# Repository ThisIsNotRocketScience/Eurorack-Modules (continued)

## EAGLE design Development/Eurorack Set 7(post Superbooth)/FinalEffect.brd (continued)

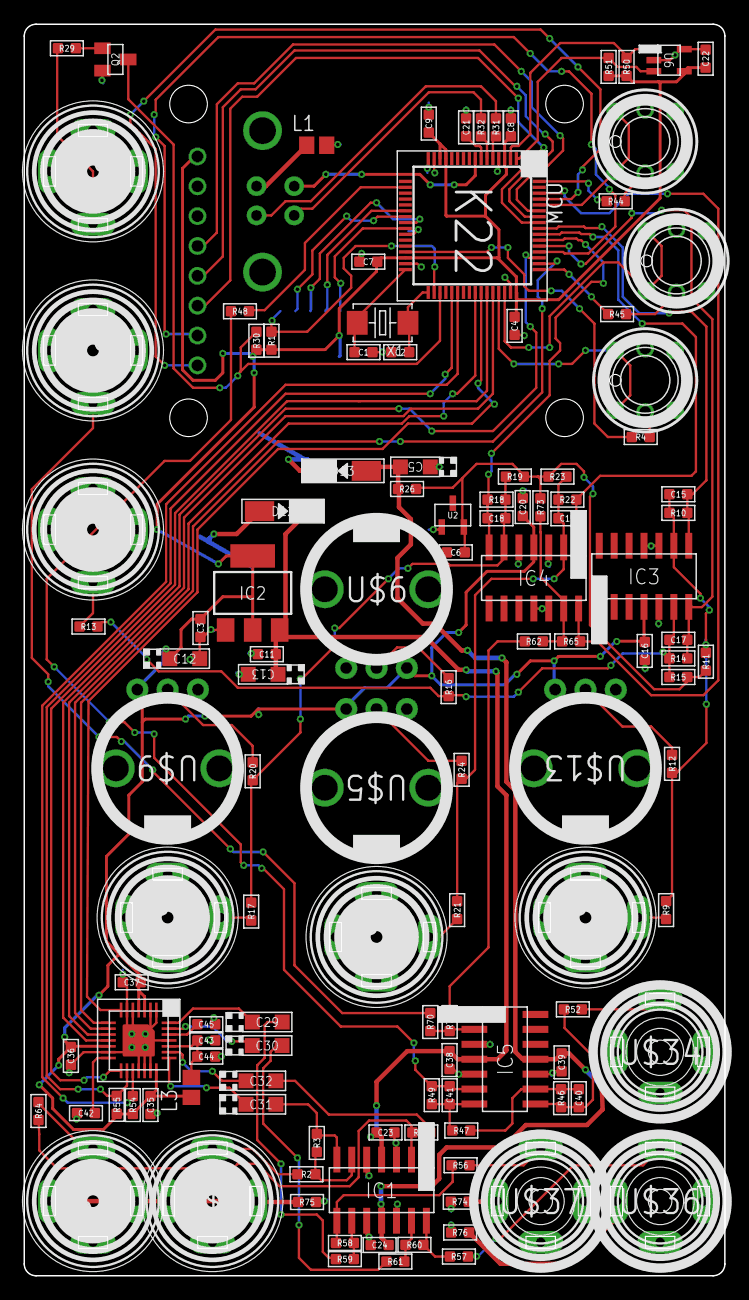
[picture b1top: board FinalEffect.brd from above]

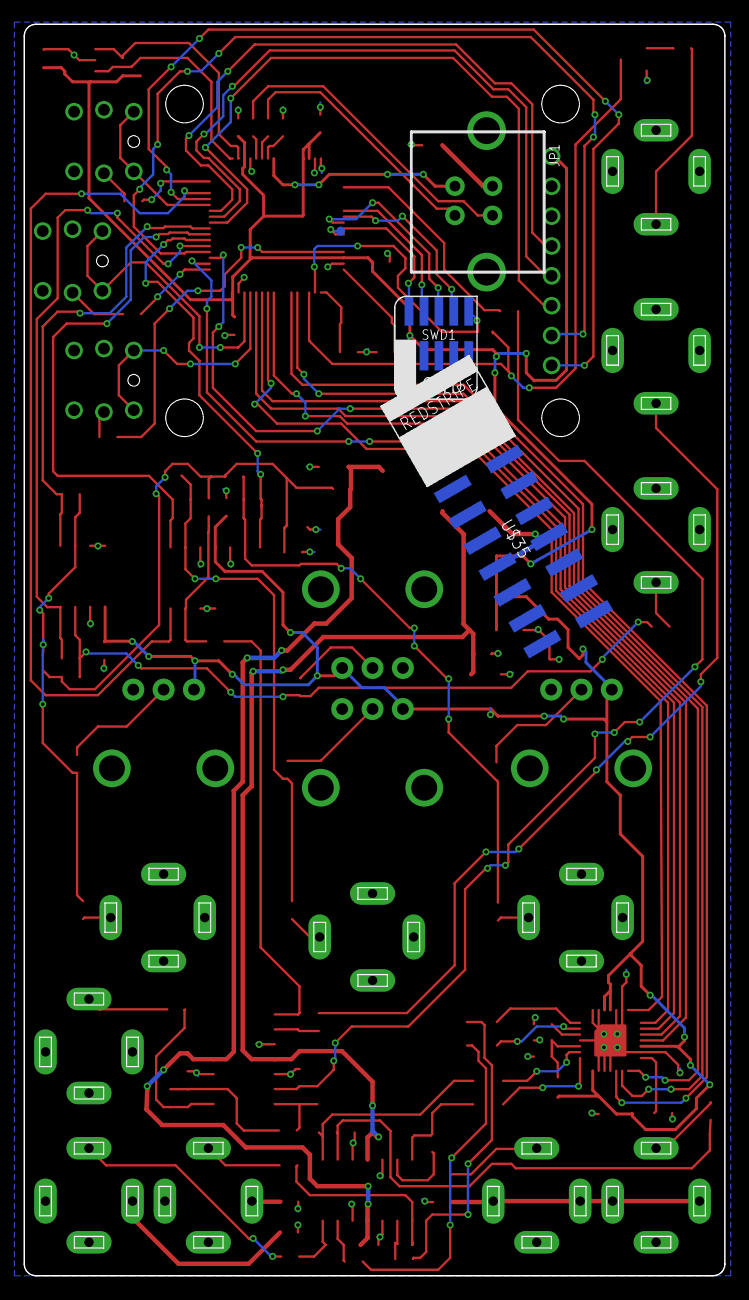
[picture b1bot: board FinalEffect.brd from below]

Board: 2 copper layers, 59.6 x 106.5 mm, 128 parts (4 on the bottom side), 100 nets.

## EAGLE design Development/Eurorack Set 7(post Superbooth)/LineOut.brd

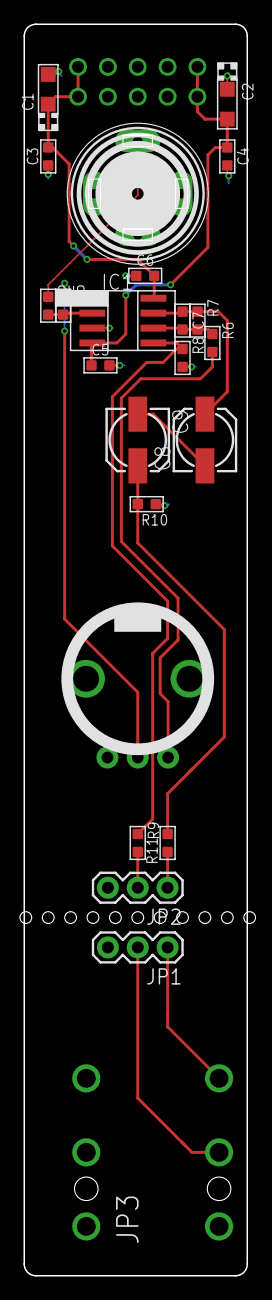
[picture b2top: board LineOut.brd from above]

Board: 2 copper layers, 19.0 x 106.5 mm, 25 parts (1 on the bottom side), 17 nets.

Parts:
C1, C2: 10uF; AVX-A
C3, C4, C5, C6: 100nF; C0603
C7: 22p; C0603
C8, C9: 220uF; 153CLV-0505
IC1: NE5532D; SO08
JP1, JP2: 1X03
JP3: AUDIO-JACK-.25-INCH-HORIZ-PTH
R2: 100k; R0603
R5: 220k; R0603
R6, R7: 4.7k; R0603
R8, R9: 27; R0603
R10: 22k; R0603
R11: 56; R0603
U$1: POWER_SIMPLE10; POWER_10
U$3: 10k; OG-POTS_ALPS_POT_VERTICAL
U$5: PJ-341; 3.5MM-JACK-SWITCH-13MM-INPUT
U$6: EURORACK_PCB4HP; EURORACK4HPPCB

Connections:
+12V: C1.+, C3.2, C6.2, IC1.8, U$1.9, U$1.10
-12V: C2.-, C4.1, C5.1, IC1.4, U$1.1, U$1.2
GND: C1.-, C2.+, C3.1, C4.2, C5.2, C6.1, IC1.3, JP2.3, R8.2, R10.1, U$1.3, U$1.4, U$1.5, U$1.6, U$1.7, U$1.8, U$3.P$1, U$5.RING@3, U$5.SWITCH@3
GND2: JP1.3, JP3.P$2, JP3.P$5
unnamed: JP2.1, R11.1
unnamed: JP1.1, JP3.P$6
unnamed: C9.+, R10.2, R11.2
unnamed: C7.1, C8.+, IC1.7, R7.1
unnamed: IC1.5, R8.1, R9.1
unnamed: JP2.2, R9.2
unnamed: C7.2, IC1.6, R6.1, R7.2
unnamed: IC1.2, R2.2, R5.2
unnamed: IC1.1, R5.1, U$3.P$2
unnamed: R6.2, U$3.P$3
unnamed: C8.-, C9.-
unnamed: R2.1, U$5.TIP@3
unnamed: JP1.2, JP3.P$4

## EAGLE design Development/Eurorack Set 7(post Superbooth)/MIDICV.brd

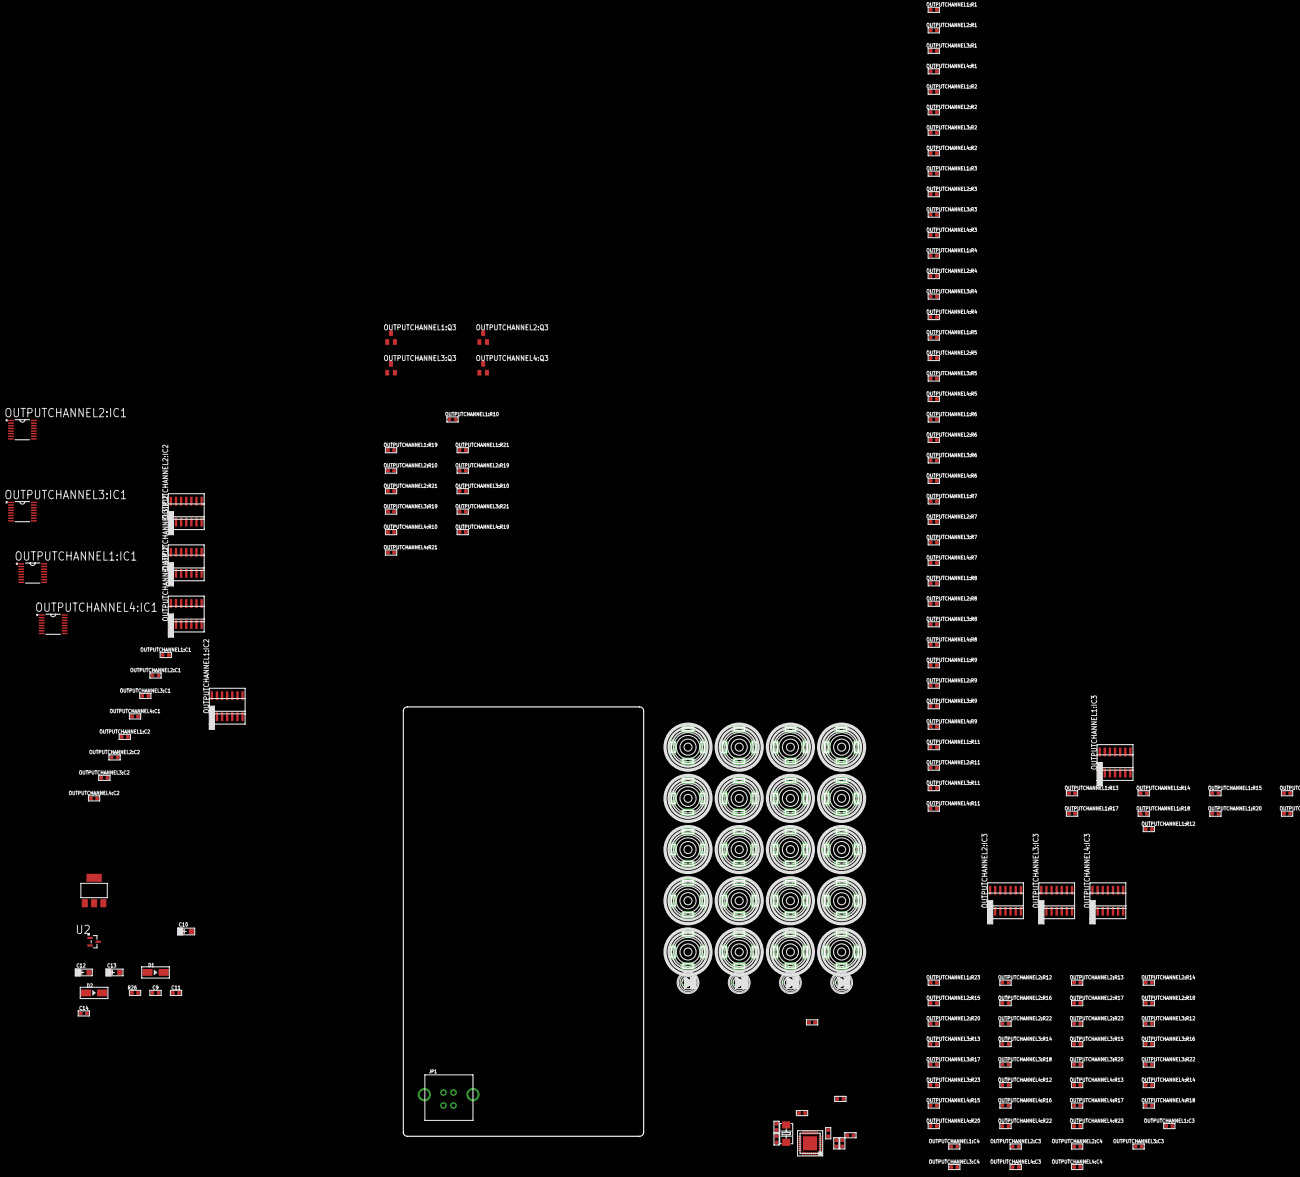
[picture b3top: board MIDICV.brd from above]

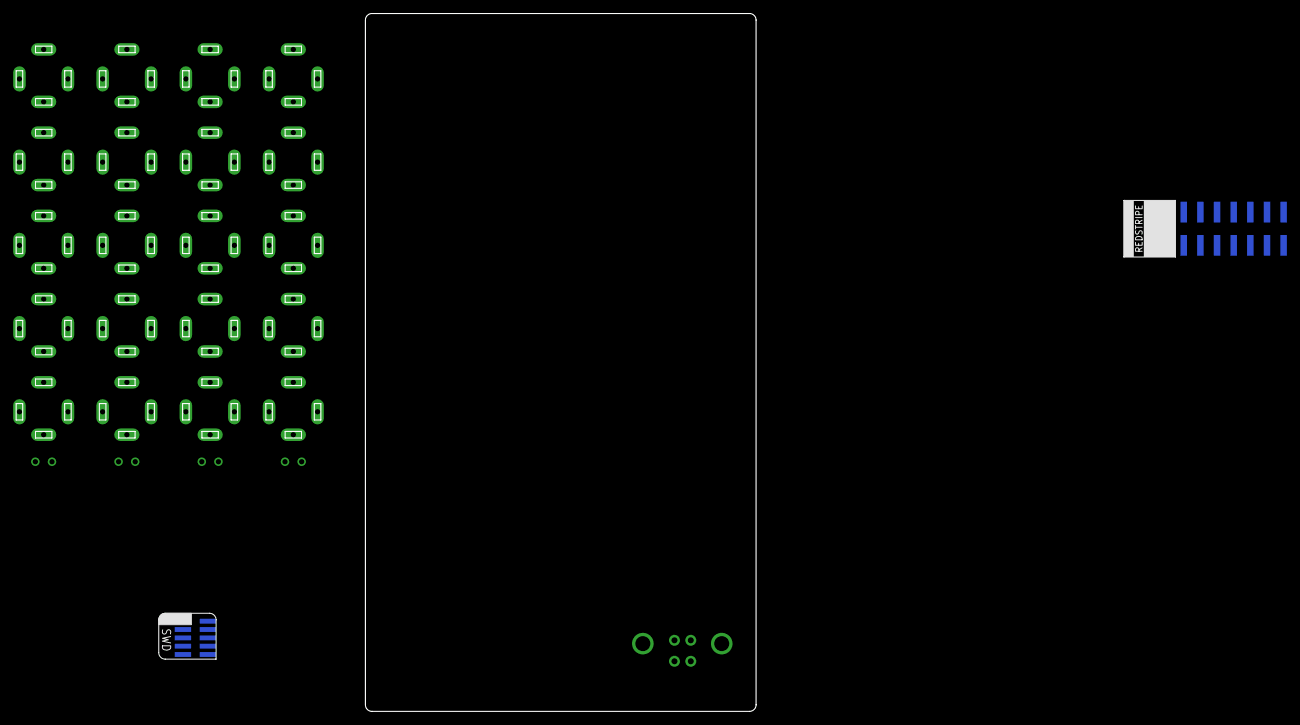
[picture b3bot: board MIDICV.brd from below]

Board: 2 copper layers, 174 parts (2 on the bottom side), 128 nets, no tracks yet.

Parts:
C1, C2, C3, C4, C6, C7, C8: C0603
C9, C11, C14: 100nF; C0603
C10, C12, C13: 10uF; AVX-A
D1, D2: MRA4004T3G; DO-214AC
IC1: LD1117AS33TR; SOT223
J14: POWERSMT; 2X08_SMT_HEADER
JP1: USBPTH-VERTICAL; USB-B-PTH-VERTICAL
OUTPUTCHANNEL1:C1, OUTPUTCHANNEL1:C2, OUTPUTCHANNEL1:C3, OUTPUTCHANNEL1:C4, OUTPUTCHANNEL2:C1, OUTPUTCHANNEL2:C2, OUTPUTCHANNEL2:C3, OUTPUTCHANNEL2:C4, OUTPUTCHANNEL3:C1, OUTPUTCHANNEL3:C2, OUTPUTCHANNEL3:C3, OUTPUTCHANNEL3:C4, OUTPUTCHANNEL4:C1, OUTPUTCHANNEL4:C2, OUTPUTCHANNEL4:C3, OUTPUTCHANNEL4:C4: C0603
OUTPUTCHANNEL1:D40, OUTPUTCHANNEL2:D40, OUTPUTCHANNEL3:D40, OUTPUTCHANNEL4:D40: yellow; 3MMLED
OUTPUTCHANNEL1:IC1, OUTPUTCHANNEL2:IC1, OUTPUTCHANNEL3:IC1, OUTPUTCHANNEL4:IC1: DAC8564; SOP65P640X110-16N
OUTPUTCHANNEL1:IC2, OUTPUTCHANNEL1:IC3, OUTPUTCHANNEL2:IC2, OUTPUTCHANNEL2:IC3, OUTPUTCHANNEL3:IC2, OUTPUTCHANNEL3:IC3, OUTPUTCHANNEL4:IC2, OUTPUTCHANNEL4:IC3: TL074D; SO14
OUTPUTCHANNEL1:Q3, OUTPUTCHANNEL2:Q3, OUTPUTCHANNEL3:Q3, OUTPUTCHANNEL4:Q3: MMBT3904; SOT23-BEC
OUTPUTCHANNEL1:R1, OUTPUTCHANNEL1:R2, OUTPUTCHANNEL1:R3, OUTPUTCHANNEL1:R4, OUTPUTCHANNEL1:R5, OUTPUTCHANNEL1:R6, OUTPUTCHANNEL1:R7, OUTPUTCHANNEL1:R8, OUTPUTCHANNEL1:R9, OUTPUTCHANNEL1:R11, OUTPUTCHANNEL1:R12, OUTPUTCHANNEL1:R13, OUTPUTCHANNEL1:R14, OUTPUTCHANNEL1:R15, OUTPUTCHANNEL1:R16, OUTPUTCHANNEL1:R17, OUTPUTCHANNEL1:R18, OUTPUTCHANNEL1:R20, OUTPUTCHANNEL1:R21, OUTPUTCHANNEL1:R22, OUTPUTCHANNEL1:R23, OUTPUTCHANNEL2:R1, OUTPUTCHANNEL2:R2, OUTPUTCHANNEL2:R3, OUTPUTCHANNEL2:R4, OUTPUTCHANNEL2:R5, OUTPUTCHANNEL2:R6, OUTPUTCHANNEL2:R7, OUTPUTCHANNEL2:R8, OUTPUTCHANNEL2:R9, OUTPUTCHANNEL2:R11, OUTPUTCHANNEL2:R12, OUTPUTCHANNEL2:R13, OUTPUTCHANNEL2:R14, OUTPUTCHANNEL2:R15, OUTPUTCHANNEL2:R16, OUTPUTCHANNEL2:R17, OUTPUTCHANNEL2:R18, OUTPUTCHANNEL2:R20, OUTPUTCHANNEL2:R21, OUTPUTCHANNEL2:R22, OUTPUTCHANNEL2:R23, OUTPUTCHANNEL3:R1, OUTPUTCHANNEL3:R2, OUTPUTCHANNEL3:R3, OUTPUTCHANNEL3:R4, OUTPUTCHANNEL3:R5, OUTPUTCHANNEL3:R6, OUTPUTCHANNEL3:R7, OUTPUTCHANNEL3:R8, OUTPUTCHANNEL3:R9, OUTPUTCHANNEL3:R11, OUTPUTCHANNEL3:R12, OUTPUTCHANNEL3:R13, OUTPUTCHANNEL3:R14, OUTPUTCHANNEL3:R15, OUTPUTCHANNEL3:R16, OUTPUTCHANNEL3:R17, OUTPUTCHANNEL3:R18, OUTPUTCHANNEL3:R20, OUTPUTCHANNEL3:R21, OUTPUTCHANNEL3:R22, OUTPUTCHANNEL3:R23, OUTPUTCHANNEL4:R1, OUTPUTCHANNEL4:R2, OUTPUTCHANNEL4:R3, OUTPUTCHANNEL4:R4, OUTPUTCHANNEL4:R5, OUTPUTCHANNEL4:R6, OUTPUTCHANNEL4:R7, OUTPUTCHANNEL4:R8, OUTPUTCHANNEL4:R9, OUTPUTCHANNEL4:R11, OUTPUTCHANNEL4:R12, OUTPUTCHANNEL4:R13, OUTPUTCHANNEL4:R14, OUTPUTCHANNEL4:R15, OUTPUTCHANNEL4:R16, OUTPUTCHANNEL4:R17, OUTPUTCHANNEL4:R18, OUTPUTCHANNEL4:R20, OUTPUTCHANNEL4:R21, OUTPUTCHANNEL4:R22, OUTPUTCHANNEL4:R23: 100k; R0603
OUTPUTCHANNEL1:R10, OUTPUTCHANNEL2:R10, OUTPUTCHANNEL3:R10, OUTPUTCHANNEL4:R10: 56; R0603
OUTPUTCHANNEL1:R19, OUTPUTCHANNEL2:R19, OUTPUTCHANNEL3:R19, OUTPUTCHANNEL4:R19: 10k; R0603
OUTPUTCHANNEL1:U$1, OUTPUTCHANNEL1:U$2, OUTPUTCHANNEL1:U$3, OUTPUTCHANNEL1:U$4, OUTPUTCHANNEL1:U$5, OUTPUTCHANNEL2:U$1, OUTPUTCHANNEL2:U$2, OUTPUTCHANNEL2:U$3, OUTPUTCHANNEL2:U$4, OUTPUTCHANNEL2:U$5, OUTPUTCHANNEL3:U$1, OUTPUTCHANNEL3:U$2, OUTPUTCHANNEL3:U$3, OUTPUTCHANNEL3:U$4, OUTPUTCHANNEL3:U$5, OUTPUTCHANNEL4:U$1, OUTPUTCHANNEL4:U$2, OUTPUTCHANNEL4:U$3, OUTPUTCHANNEL4:U$4, OUTPUTCHANNEL4:U$5: PJ-341; 3.5MM-JACK-SWITCH-13MM-OUTPUT
R1, R2: 33; R0603
R26: 10k; R0603
SWD1: CORTEX_SWD; M50-3600542
U2: LM4040DIM3-5.0; SOT95P237X112-3N
U$1: KL26X32VFM4; QFN-32
U$2: EURORACK_PCB12HP; EURORACK12HPPCB
X2: CRYSTAL-0500290P1; 2P-SMD-5.0X3.2

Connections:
3.3V: C1.1, C2.1, C3.1, C4.1, C8.1, C9.2, C12.+, IC1.2, IC1.4, SWD1.1, U$1.7, U$1.15
12V: C11.2, C13.+, D1.2, IC1.3, OUTPUTCHANNEL1:C1.1, OUTPUTCHANNEL1:C3.1, OUTPUTCHANNEL1:IC2.4, OUTPUTCHANNEL1:IC3.4, OUTPUTCHANNEL1:R19.2, OUTPUTCHANNEL2:C1.1, OUTPUTCHANNEL2:C3.1, OUTPUTCHANNEL2:IC2.4, OUTPUTCHANNEL2:IC3.4, OUTPUTCHANNEL2:R19.2, OUTPUTCHANNEL3:C1.1, OUTPUTCHANNEL3:C3.1, OUTPUTCHANNEL3:IC2.4, OUTPUTCHANNEL3:IC3.4, OUTPUTCHANNEL3:R19.2, OUTPUTCHANNEL4:C1.1, OUTPUTCHANNEL4:C3.1, OUTPUTCHANNEL4:IC2.4, OUTPUTCHANNEL4:IC3.4, OUTPUTCHANNEL4:R19.2
-12V: C10.-, D2.1, OUTPUTCHANNEL1:C2.1, OUTPUTCHANNEL1:C4.1, OUTPUTCHANNEL1:IC2.11, OUTPUTCHANNEL1:IC3.11, OUTPUTCHANNEL2:C2.1, OUTPUTCHANNEL2:C4.1, OUTPUTCHANNEL2:IC2.11, OUTPUTCHANNEL2:IC3.11, OUTPUTCHANNEL3:C2.1, OUTPUTCHANNEL3:C4.1, OUTPUTCHANNEL3:IC2.11, OUTPUTCHANNEL3:IC3.11, OUTPUTCHANNEL4:C2.1, OUTPUTCHANNEL4:C4.1, OUTPUTCHANNEL4:IC2.11, OUTPUTCHANNEL4:IC3.11, R26.1
BUTTON4: SWD1.10, U$1.19
EXTCV: J14.13, J14.14, OUTPUTCHANNEL1:R2.2, OUTPUTCHANNEL1:U$1.TIP@3
EXTGATE: J14.15, J14.16, OUTPUTCHANNEL1:R10.2, OUTPUTCHANNEL1:R21.1
GND: C1.2, C2.2, C3.2, C4.2, C6.1, C7.2, C8.2, C9.1, C10.+, C11.1, C12.-, C13.-, C14.1, IC1.1, J14.3, J14.4, J14.5, J14.6, J14.7, J14.8, JP1.GND, OUTPUTCHANNEL1:C1.2, OUTPUTCHANNEL1:C2.2, OUTPUTCHANNEL1:C3.2, OUTPUTCHANNEL1:C4.2, OUTPUTCHANNEL1:IC1.6, OUTPUTCHANNEL1:IC2.3, OUTPUTCHANNEL1:IC2.5, OUTPUTCHANNEL1:IC2.10, OUTPUTCHANNEL1:IC2.12, OUTPUTCHANNEL1:IC3.3, OUTPUTCHANNEL1:IC3.5, OUTPUTCHANNEL1:IC3.10, OUTPUTCHANNEL1:IC3.12, OUTPUTCHANNEL1:Q3.E, OUTPUTCHANNEL1:U$1.RING@3, OUTPUTCHANNEL1:U$2.RING@3, OUTPUTCHANNEL1:U$3.RING@3, OUTPUTCHANNEL1:U$4.RING@3, OUTPUTCHANNEL1:U$5.RING@3, OUTPUTCHANNEL2:C1.2, OUTPUTCHANNEL2:C2.2, OUTPUTCHANNEL2:C3.2, OUTPUTCHANNEL2:C4.2, OUTPUTCHANNEL2:IC1.6, OUTPUTCHANNEL2:IC2.3, OUTPUTCHANNEL2:IC2.5, OUTPUTCHANNEL2:IC2.10, OUTPUTCHANNEL2:IC2.12, OUTPUTCHANNEL2:IC3.3, OUTPUTCHANNEL2:IC3.5, OUTPUTCHANNEL2:IC3.10, OUTPUTCHANNEL2:IC3.12, OUTPUTCHANNEL2:Q3.E, OUTPUTCHANNEL2:U$1.RING@3, OUTPUTCHANNEL2:U$2.RING@3, OUTPUTCHANNEL2:U$3.RING@3, OUTPUTCHANNEL2:U$4.RING@3, OUTPUTCHANNEL2:U$5.RING@3, OUTPUTCHANNEL3:C1.2, OUTPUTCHANNEL3:C2.2, OUTPUTCHANNEL3:C3.2, OUTPUTCHANNEL3:C4.2, OUTPUTCHANNEL3:IC1.6, OUTPUTCHANNEL3:IC2.3, OUTPUTCHANNEL3:IC2.5, OUTPUTCHANNEL3:IC2.10, OUTPUTCHANNEL3:IC2.12, OUTPUTCHANNEL3:IC3.3, OUTPUTCHANNEL3:IC3.5, OUTPUTCHANNEL3:IC3.10, OUTPUTCHANNEL3:IC3.12, OUTPUTCHANNEL3:Q3.E, OUTPUTCHANNEL3:U$1.RING@3, OUTPUTCHANNEL3:U$2.RING@3, OUTPUTCHANNEL3:U$3.RING@3, OUTPUTCHANNEL3:U$4.RING@3, OUTPUTCHANNEL3:U$5.RING@3, OUTPUTCHANNEL4:C1.2, OUTPUTCHANNEL4:C2.2, OUTPUTCHANNEL4:C3.2, OUTPUTCHANNEL4:C4.2, OUTPUTCHANNEL4:IC1.6, OUTPUTCHANNEL4:IC2.3, OUTPUTCHANNEL4:IC2.5, OUTPUTCHANNEL4:IC2.10, OUTPUTCHANNEL4:IC2.12, OUTPUTCHANNEL4:IC3.3, OUTPUTCHANNEL4:IC3.5, OUTPUTCHANNEL4:IC3.10, OUTPUTCHANNEL4:IC3.12, OUTPUTCHANNEL4:Q3.E, OUTPUTCHANNEL4:U$1.RING@3, OUTPUTCHANNEL4:U$2.RING@3, OUTPUTCHANNEL4:U$3.RING@3, OUTPUTCHANNEL4:U$4.RING@3, OUTPUTCHANNEL4:U$5.RING@3, SWD1.3, SWD1.5, SWD1.9, U2.1, U$1.2, U$1.8, U$1.16, U$1.GROUNDPAD
unnamed: JP1.D-, R2.1
unnamed: JP1.D+, R1.1
unnamed: R1.2, U$1.3
unnamed: R2.2, U$1.4
unnamed: OUTPUTCHANNEL2:R10.2, OUTPUTCHANNEL2:R21.1
unnamed: OUTPUTCHANNEL3:R10.2, OUTPUTCHANNEL3:R21.1
unnamed: OUTPUTCHANNEL4:R10.2, OUTPUTCHANNEL4:R21.1
unnamed: C6.2, U$1.17, X2.2
unnamed: C7.1, U$1.18, X2.1
unnamed: D1.1, J14.9, J14.10
unnamed: D2.2, J14.1, J14.2
OUTPUTCHANNEL1:MOD: OUTPUTCHANNEL1:R13.2, OUTPUTCHANNEL1:U$4.TIP@3
OUTPUTCHANNEL1:N$5: OUTPUTCHANNEL1:IC2.6, OUTPUTCHANNEL1:R1.2, OUTPUTCHANNEL1:R9.1
OUTPUTCHANNEL1:N$6: OUTPUTCHANNEL1:IC2.13, OUTPUTCHANNEL1:R4.2, OUTPUTCHANNEL1:R8.1
OUTPUTCHANNEL1:N$8: OUTPUTCHANNEL1:IC2.14, OUTPUTCHANNEL1:R3.1, OUTPUTCHANNEL1:R8.2
OUTPUTCHANNEL1:N$9: OUTPUTCHANNEL1:IC2.7, OUTPUTCHANNEL1:R2.1, OUTPUTCHANNEL1:R9.2
OUTPUTCHANNEL1:N$11: OUTPUTCHANNEL1:IC2.1, OUTPUTCHANNEL1:R1.1, OUTPUTCHANNEL1:R11.2
OUTPUTCHANNEL1:N$12: OUTPUTCHANNEL1:IC2.8, OUTPUTCHANNEL1:R4.1, OUTPUTCHANNEL1:R7.2
OUTPUTCHANNEL1:N$13: OUTPUTCHANNEL1:IC2.2, OUTPUTCHANNEL1:R5.2, OUTPUTCHANNEL1:R11.1
OUTPUTCHANNEL1:N$14: OUTPUTCHANNEL1:IC2.9, OUTPUTCHANNEL1:R6.2, OUTPUTCHANNEL1:R7.1
OUTPUTCHANNEL1:N$15: OUTPUTCHANNEL1:IC1.2, OUTPUTCHANNEL1:R6.1
OUTPUTCHANNEL1:N$16: OUTPUTCHANNEL1:IC1.1, OUTPUTCHANNEL1:R5.1
OUTPUTCHANNEL1:N$17: OUTPUTCHANNEL1:IC3.6, OUTPUTCHANNEL1:R12.2, OUTPUTCHANNEL1:R22.1
OUTPUTCHANNEL1:N$18: OUTPUTCHANNEL1:IC3.13, OUTPUTCHANNEL1:R15.2, OUTPUTCHANNEL1:R20.1
OUTPUTCHANNEL1:N$20: OUTPUTCHANNEL1:IC3.14, OUTPUTCHANNEL1:R14.1, OUTPUTCHANNEL1:R20.2
OUTPUTCHANNEL1:N$21: OUTPUTCHANNEL1:IC3.7, OUTPUTCHANNEL1:R13.1, OUTPUTCHANNEL1:R22.2
OUTPUTCHANNEL1:N$23: OUTPUTCHANNEL1:D40.-, OUTPUTCHANNEL1:R10.1
OUTPUTCHANNEL1:N$24: OUTPUTCHANNEL1:IC3.1, OUTPUTCHANNEL1:R12.1, OUTPUTCHANNEL1:R23.2
OUTPUTCHANNEL1:N$25: OUTPUTCHANNEL1:Q3.B, OUTPUTCHANNEL1:R21.2
OUTPUTCHANNEL1:N$26: OUTPUTCHANNEL1:IC3.8, OUTPUTCHANNEL1:R15.1, OUTPUTCHANNEL1:R18.2
OUTPUTCHANNEL1:N$27: OUTPUTCHANNEL1:IC3.2, OUTPUTCHANNEL1:R16.2, OUTPUTCHANNEL1:R23.1
OUTPUTCHANNEL1:N$28: OUTPUTCHANNEL1:IC3.9, OUTPUTCHANNEL1:R17.2, OUTPUTCHANNEL1:R18.1
OUTPUTCHANNEL1:N$29: OUTPUTCHANNEL1:Q3.C, OUTPUTCHANNEL1:R19.1, OUTPUTCHANNEL1:U$2.TIP@3
OUTPUTCHANNEL1:N$30: OUTPUTCHANNEL1:IC1.8, OUTPUTCHANNEL1:R17.1
OUTPUTCHANNEL1:N$31: OUTPUTCHANNEL1:IC1.7, OUTPUTCHANNEL1:R16.1
OUTPUTCHANNEL1:PITCH: OUTPUTCHANNEL1:R14.2, OUTPUTCHANNEL1:U$5.TIP@3
OUTPUTCHANNEL1:VELOCITY: OUTPUTCHANNEL1:R3.2, OUTPUTCHANNEL1:U$3.TIP@3
OUTPUTCHANNEL2:CV_OUT: OUTPUTCHANNEL2:R2.2, OUTPUTCHANNEL2:U$1.TIP@3
OUTPUTCHANNEL2:MOD: OUTPUTCHANNEL2:R13.2, OUTPUTCHANNEL2:U$4.TIP@3
OUTPUTCHANNEL2:N$5: OUTPUTCHANNEL2:IC2.6, OUTPUTCHANNEL2:R1.2, OUTPUTCHANNEL2:R9.1
OUTPUTCHANNEL2:N$6: OUTPUTCHANNEL2:IC2.13, OUTPUTCHANNEL2:R4.2, OUTPUTCHANNEL2:R8.1
OUTPUTCHANNEL2:N$8: OUTPUTCHANNEL2:IC2.14, OUTPUTCHANNEL2:R3.1, OUTPUTCHANNEL2:R8.2
OUTPUTCHANNEL2:N$9: OUTPUTCHANNEL2:IC2.7, OUTPUTCHANNEL2:R2.1, OUTPUTCHANNEL2:R9.2
OUTPUTCHANNEL2:N$11: OUTPUTCHANNEL2:IC2.1, OUTPUTCHANNEL2:R1.1, OUTPUTCHANNEL2:R11.2
OUTPUTCHANNEL2:N$12: OUTPUTCHANNEL2:IC2.8, OUTPUTCHANNEL2:R4.1, OUTPUTCHANNEL2:R7.2
OUTPUTCHANNEL2:N$13: OUTPUTCHANNEL2:IC2.2, OUTPUTCHANNEL2:R5.2, OUTPUTCHANNEL2:R11.1
OUTPUTCHANNEL2:N$14: OUTPUTCHANNEL2:IC2.9, OUTPUTCHANNEL2:R6.2, OUTPUTCHANNEL2:R7.1
OUTPUTCHANNEL2:N$15: OUTPUTCHANNEL2:IC1.2, OUTPUTCHANNEL2:R6.1
OUTPUTCHANNEL2:N$16: OUTPUTCHANNEL2:IC1.1, OUTPUTCHANNEL2:R5.1
OUTPUTCHANNEL2:N$17: OUTPUTCHANNEL2:IC3.6, OUTPUTCHANNEL2:R12.2, OUTPUTCHANNEL2:R22.1
OUTPUTCHANNEL2:N$18: OUTPUTCHANNEL2:IC3.13, OUTPUTCHANNEL2:R15.2, OUTPUTCHANNEL2:R20.1
OUTPUTCHANNEL2:N$20: OUTPUTCHANNEL2:IC3.14, OUTPUTCHANNEL2:R14.1, OUTPUTCHANNEL2:R20.2
OUTPUTCHANNEL2:N$21: OUTPUTCHANNEL2:IC3.7, OUTPUTCHANNEL2:R13.1, OUTPUTCHANNEL2:R22.2
OUTPUTCHANNEL2:N$23: OUTPUTCHANNEL2:D40.-, OUTPUTCHANNEL2:R10.1
OUTPUTCHANNEL2:N$24: OUTPUTCHANNEL2:IC3.1, OUTPUTCHANNEL2:R12.1, OUTPUTCHANNEL2:R23.2
OUTPUTCHANNEL2:N$25: OUTPUTCHANNEL2:Q3.B, OUTPUTCHANNEL2:R21.2
OUTPUTCHANNEL2:N$26: OUTPUTCHANNEL2:IC3.8, OUTPUTCHANNEL2:R15.1, OUTPUTCHANNEL2:R18.2
OUTPUTCHANNEL2:N$27: OUTPUTCHANNEL2:IC3.2, OUTPUTCHANNEL2:R16.2, OUTPUTCHANNEL2:R23.1
OUTPUTCHANNEL2:N$28: OUTPUTCHANNEL2:IC3.9, OUTPUTCHANNEL2:R17.2, OUTPUTCHANNEL2:R18.1
OUTPUTCHANNEL2:N$29: OUTPUTCHANNEL2:Q3.C, OUTPUTCHANNEL2:R19.1, OUTPUTCHANNEL2:U$2.TIP@3
OUTPUTCHANNEL2:N$30: OUTPUTCHANNEL2:IC1.8, OUTPUTCHANNEL2:R17.1
OUTPUTCHANNEL2:N$31: OUTPUTCHANNEL2:IC1.7, OUTPUTCHANNEL2:R16.1
OUTPUTCHANNEL2:PITCH: OUTPUTCHANNEL2:R14.2, OUTPUTCHANNEL2:U$5.TIP@3
OUTPUTCHANNEL2:VELOCITY: OUTPUTCHANNEL2:R3.2, OUTPUTCHANNEL2:U$3.TIP@3
OUTPUTCHANNEL3:CV_OUT: OUTPUTCHANNEL3:R2.2, OUTPUTCHANNEL3:U$1.TIP@3
OUTPUTCHANNEL3:MOD: OUTPUTCHANNEL3:R13.2, OUTPUTCHANNEL3:U$4.TIP@3
OUTPUTCHANNEL3:N$5: OUTPUTCHANNEL3:IC2.6, OUTPUTCHANNEL3:R1.2, OUTPUTCHANNEL3:R9.1
OUTPUTCHANNEL3:N$6: OUTPUTCHANNEL3:IC2.13, OUTPUTCHANNEL3:R4.2, OUTPUTCHANNEL3:R8.1
OUTPUTCHANNEL3:N$8: OUTPUTCHANNEL3:IC2.14, OUTPUTCHANNEL3:R3.1, OUTPUTCHANNEL3:R8.2
OUTPUTCHANNEL3:N$9: OUTPUTCHANNEL3:IC2.7, OUTPUTCHANNEL3:R2.1, OUTPUTCHANNEL3:R9.2
OUTPUTCHANNEL3:N$11: OUTPUTCHANNEL3:IC2.1, OUTPUTCHANNEL3:R1.1, OUTPUTCHANNEL3:R11.2
OUTPUTCHANNEL3:N$12: OUTPUTCHANNEL3:IC2.8, OUTPUTCHANNEL3:R4.1, OUTPUTCHANNEL3:R7.2
OUTPUTCHANNEL3:N$13: OUTPUTCHANNEL3:IC2.2, OUTPUTCHANNEL3:R5.2, OUTPUTCHANNEL3:R11.1
OUTPUTCHANNEL3:N$14: OUTPUTCHANNEL3:IC2.9, OUTPUTCHANNEL3:R6.2, OUTPUTCHANNEL3:R7.1
OUTPUTCHANNEL3:N$15: OUTPUTCHANNEL3:IC1.2, OUTPUTCHANNEL3:R6.1
OUTPUTCHANNEL3:N$16: OUTPUTCHANNEL3:IC1.1, OUTPUTCHANNEL3:R5.1
OUTPUTCHANNEL3:N$17: OUTPUTCHANNEL3:IC3.6, OUTPUTCHANNEL3:R12.2, OUTPUTCHANNEL3:R22.1
OUTPUTCHANNEL3:N$18: OUTPUTCHANNEL3:IC3.13, OUTPUTCHANNEL3:R15.2, OUTPUTCHANNEL3:R20.1
OUTPUTCHANNEL3:N$20: OUTPUTCHANNEL3:IC3.14, OUTPUTCHANNEL3:R14.1, OUTPUTCHANNEL3:R20.2
OUTPUTCHANNEL3:N$21: OUTPUTCHANNEL3:IC3.7, OUTPUTCHANNEL3:R13.1, OUTPUTCHANNEL3:R22.2
OUTPUTCHANNEL3:N$23: OUTPUTCHANNEL3:D40.-, OUTPUTCHANNEL3:R10.1
OUTPUTCHANNEL3:N$24: OUTPUTCHANNEL3:IC3.1, OUTPUTCHANNEL3:R12.1, OUTPUTCHANNEL3:R23.2
OUTPUTCHANNEL3:N$25: OUTPUTCHANNEL3:Q3.B, OUTPUTCHANNEL3:R21.2
OUTPUTCHANNEL3:N$26: OUTPUTCHANNEL3:IC3.8, OUTPUTCHANNEL3:R15.1, OUTPUTCHANNEL3:R18.2
OUTPUTCHANNEL3:N$27: OUTPUTCHANNEL3:IC3.2, OUTPUTCHANNEL3:R16.2, OUTPUTCHANNEL3:R23.1
OUTPUTCHANNEL3:N$28: OUTPUTCHANNEL3:IC3.9, OUTPUTCHANNEL3:R17.2, OUTPUTCHANNEL3:R18.1
OUTPUTCHANNEL3:N$29: OUTPUTCHANNEL3:Q3.C, OUTPUTCHANNEL3:R19.1, OUTPUTCHANNEL3:U$2.TIP@3
OUTPUTCHANNEL3:N$30: OUTPUTCHANNEL3:IC1.8, OUTPUTCHANNEL3:R17.1
OUTPUTCHANNEL3:N$31: OUTPUTCHANNEL3:IC1.7, OUTPUTCHANNEL3:R16.1
OUTPUTCHANNEL3:PITCH: OUTPUTCHANNEL3:R14.2, OUTPUTCHANNEL3:U$5.TIP@3
OUTPUTCHANNEL3:VELOCITY: OUTPUTCHANNEL3:R3.2, OUTPUTCHANNEL3:U$3.TIP@3
OUTPUTCHANNEL4:CV_OUT: OUTPUTCHANNEL4:R2.2, OUTPUTCHANNEL4:U$1.TIP@3
OUTPUTCHANNEL4:MOD: OUTPUTCHANNEL4:R13.2, OUTPUTCHANNEL4:U$4.TIP@3
OUTPUTCHANNEL4:N$5: OUTPUTCHANNEL4:IC2.6, OUTPUTCHANNEL4:R1.2, OUTPUTCHANNEL4:R9.1
OUTPUTCHANNEL4:N$6: OUTPUTCHANNEL4:IC2.13, OUTPUTCHANNEL4:R4.2, OUTPUTCHANNEL4:R8.1
OUTPUTCHANNEL4:N$8: OUTPUTCHANNEL4:IC2.14, OUTPUTCHANNEL4:R3.1, OUTPUTCHANNEL4:R8.2
OUTPUTCHANNEL4:N$9: OUTPUTCHANNEL4:IC2.7, OUTPUTCHANNEL4:R2.1, OUTPUTCHANNEL4:R9.2
OUTPUTCHANNEL4:N$11: OUTPUTCHANNEL4:IC2.1, OUTPUTCHANNEL4:R1.1, OUTPUTCHANNEL4:R11.2
OUTPUTCHANNEL4:N$12: OUTPUTCHANNEL4:IC2.8, OUTPUTCHANNEL4:R4.1, OUTPUTCHANNEL4:R7.2
OUTPUTCHANNEL4:N$13: OUTPUTCHANNEL4:IC2.2, OUTPUTCHANNEL4:R5.2, OUTPUTCHANNEL4:R11.1
OUTPUTCHANNEL4:N$14: OUTPUTCHANNEL4:IC2.9, OUTPUTCHANNEL4:R6.2, OUTPUTCHANNEL4:R7.1
OUTPUTCHANNEL4:N$15: OUTPUTCHANNEL4:IC1.2, OUTPUTCHANNEL4:R6.1
OUTPUTCHANNEL4:N$16: OUTPUTCHANNEL4:IC1.1, OUTPUTCHANNEL4:R5.1
OUTPUTCHANNEL4:N$17: OUTPUTCHANNEL4:IC3.6, OUTPUTCHANNEL4:R12.2, OUTPUTCHANNEL4:R22.1
OUTPUTCHANNEL4:N$18: OUTPUTCHANNEL4:IC3.13, OUTPUTCHANNEL4:R15.2, OUTPUTCHANNEL4:R20.1
OUTPUTCHANNEL4:N$20: OUTPUTCHANNEL4:IC3.14, OUTPUTCHANNEL4:R14.1, OUTPUTCHANNEL4:R20.2
OUTPUTCHANNEL4:N$21: OUTPUTCHANNEL4:IC3.7, OUTPUTCHANNEL4:R13.1, OUTPUTCHANNEL4:R22.2
OUTPUTCHANNEL4:N$23: OUTPUTCHANNEL4:D40.-, OUTPUTCHANNEL4:R10.1
OUTPUTCHANNEL4:N$24: OUTPUTCHANNEL4:IC3.1, OUTPUTCHANNEL4:R12.1, OUTPUTCHANNEL4:R23.2
OUTPUTCHANNEL4:N$25: OUTPUTCHANNEL4:Q3.B, OUTPUTCHANNEL4:R21.2
OUTPUTCHANNEL4:N$26: OUTPUTCHANNEL4:IC3.8, OUTPUTCHANNEL4:R15.1, OUTPUTCHANNEL4:R18.2
OUTPUTCHANNEL4:N$27: OUTPUTCHANNEL4:IC3.2, OUTPUTCHANNEL4:R16.2, OUTPUTCHANNEL4:R23.1
OUTPUTCHANNEL4:N$28: OUTPUTCHANNEL4:IC3.9, OUTPUTCHANNEL4:R17.2, OUTPUTCHANNEL4:R18.1
OUTPUTCHANNEL4:N$29: OUTPUTCHANNEL4:Q3.C, OUTPUTCHANNEL4:R19.1, OUTPUTCHANNEL4:U$2.TIP@3
OUTPUTCHANNEL4:N$30: OUTPUTCHANNEL4:IC1.8, OUTPUTCHANNEL4:R17.1
OUTPUTCHANNEL4:N$31: OUTPUTCHANNEL4:IC1.7, OUTPUTCHANNEL4:R16.1
OUTPUTCHANNEL4:PITCH: OUTPUTCHANNEL4:R14.2, OUTPUTCHANNEL4:U$5.TIP@3
OUTPUTCHANNEL4:VELOCITY: OUTPUTCHANNEL4:R3.2, OUTPUTCHANNEL4:U$3.TIP@3
REF_-5V: C14.2, R26.2, U2.2
SWDCLK: SWD1.4, U$1.10
SWDIO: SWD1.2, U$1.13

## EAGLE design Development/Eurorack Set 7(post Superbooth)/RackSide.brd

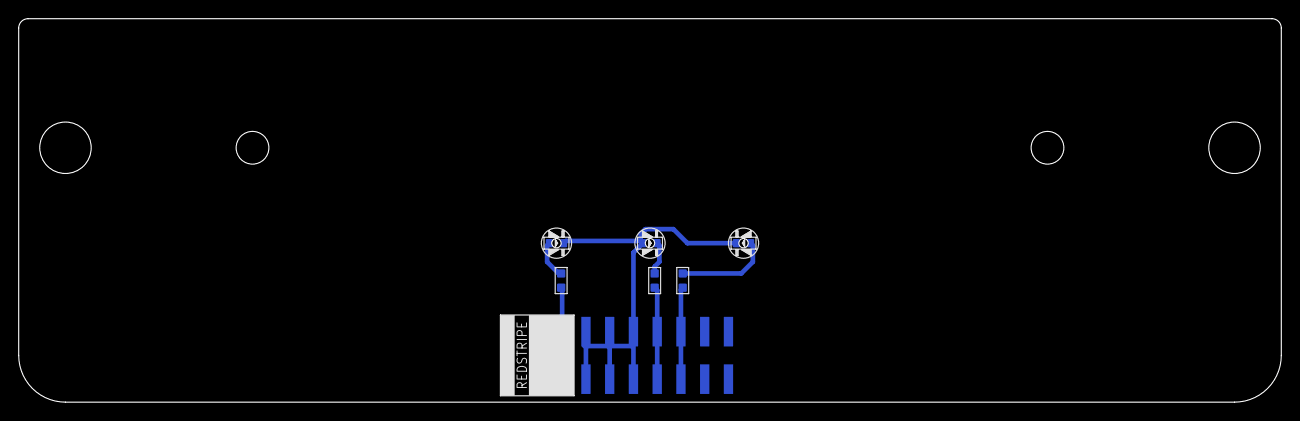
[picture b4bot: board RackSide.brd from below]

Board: 2 copper layers, 135.0 x 41.0 mm, 7 parts (7 on the bottom side), 7 nets.

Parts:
D1, D2, D3: LED0603
R1, R2, R3: R0603
U$1: POWERSMT; 2X08_SMT_HEADER

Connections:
GND: D1.+, D2.-, D3.-, U$1.3, U$1.4, U$1.5, U$1.6, U$1.7, U$1.8
unnamed: R1.1, U$1.9, U$1.10
unnamed: R2.1, U$1.1, U$1.2
unnamed: R3.1, U$1.11, U$1.12
unnamed: D1.-, R1.2
unnamed: D2.+, R2.2
unnamed: D3.+, R3.2

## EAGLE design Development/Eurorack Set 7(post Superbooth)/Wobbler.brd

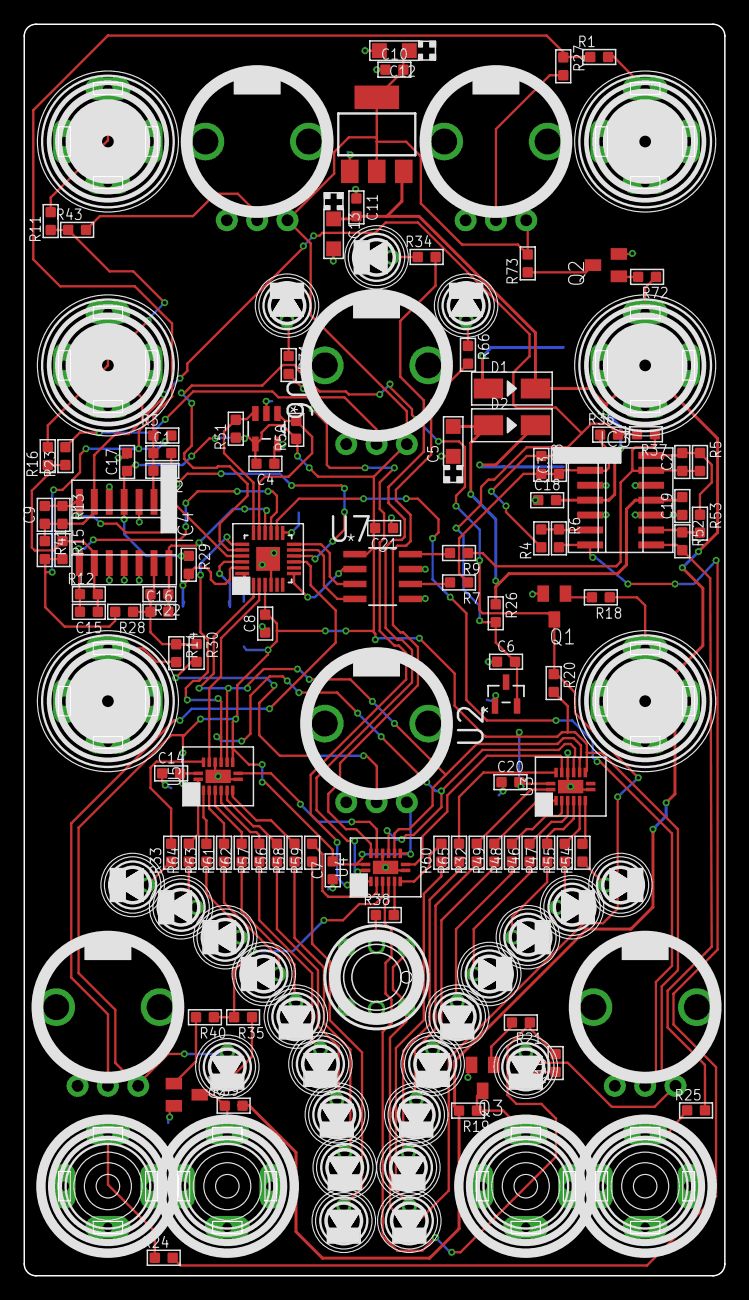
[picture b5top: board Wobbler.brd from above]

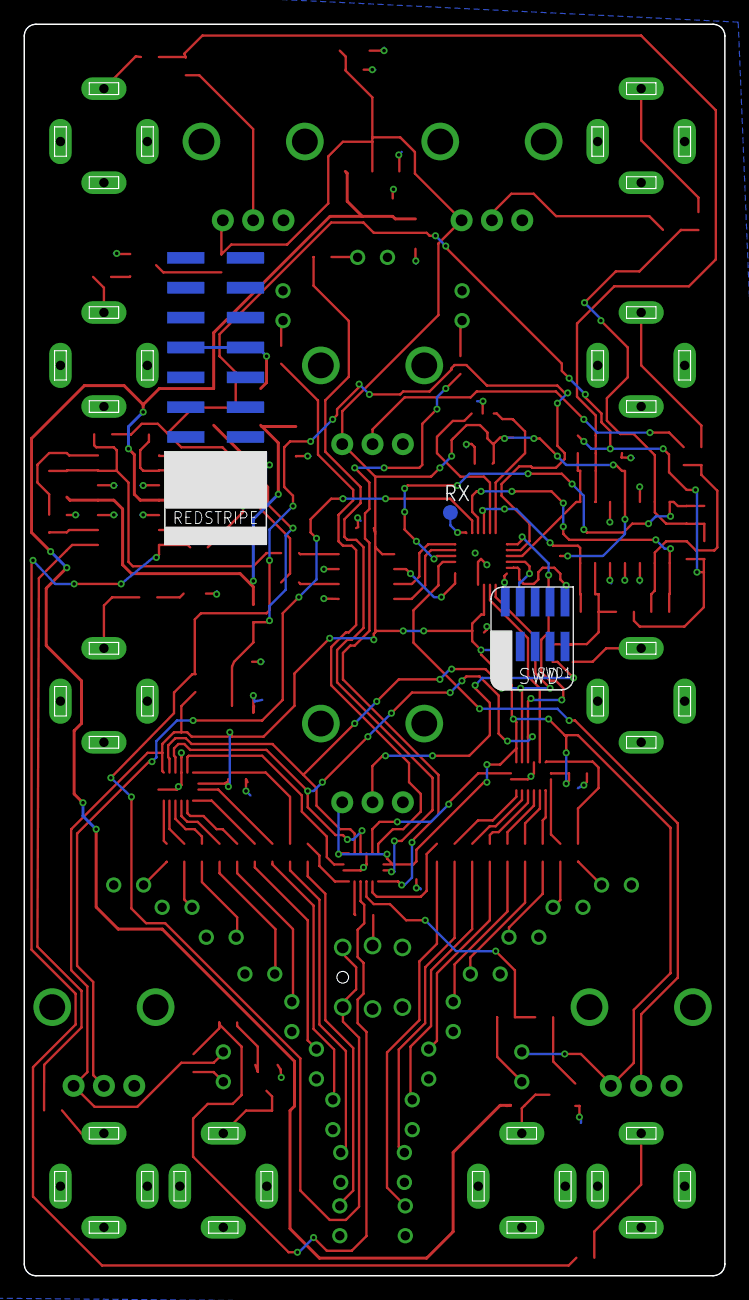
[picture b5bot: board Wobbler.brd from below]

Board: 2 copper layers, 59.6 x 106.5 mm, 145 parts (3 on the bottom side), 109 nets.

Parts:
C1, C2, C3, C9, C15, C16: 3.3nF; C0603
C4, C6, C7, C8, C10, C11, C14, C17, C18, C19, C20, C21: 100nF; C0603
C5, C12, C13: 10uF; AVX-A
D1, D2: MRA4004T3G; DO-214AC
D3, D4, D5, D6, D7, D8, D9, D10, D11, D12, D24, D25, D26, D27, D28, D29, D30, D31, D32, D33, D34, D35, D40: yellow; 3MMLED
IC1: LD1117AS33TR; SOT223
IC3: TL074D; SO14
IC4: MCP6004; SO14
J1, J2, J3, J4, J5, J8: PJ-341; 3.5MM-JACK-SWITCH-13MM-INPUT
J6, J7, J12, J13: PJ-341; 3.5MM-JACK-SWITCH-13MM-OUTPUT
J14: POWERSMT; 2X08_SMT_HEADER
OUTLINE: EURORACK_PCB12HP; EURORACK12HPPCB
Q1, Q2, Q3, Q5: MMBT3904; SOT23-BEC
R1, R4, R6, R11, R14, R16, R18, R21, R40, R52, R53, R72: 100k; R0603
R2, R12, R13, R22, R23, R27, R30, R43: 33k; R0603
R3, R15, R28, R41: 51k; R0603
R5, R8, R36, R37: 36k; R0603
R7, R9: 12k; R0603
R10, R31, R32, R33, R34, R35, R38, R46, R47, R48, R49, R54, R55, R56, R57, R58, R59, R60, R61, R62, R63, R64, R65, R66: 56; R0603
R17, R42, R44, R45, R68, R69: 10kB; OG-POTS_ALPS_POT_VERTICAL
R19, R20, R26, R29, R39, R73: 10k; R0603
R24, R25: 100; R0603
R50, R51: 2k; R0603
RX: TPB1,27; B1,27
SWD1: CORTEX_SWD; M50-3600542
U1: MKL02Z32VFK4; QFN50P400X400X100-25N
U2: LM4040DIM3-5.0; SOT95P237X112-3N
U3, U4, U5: 74HC595BQ; QFN50P250X350X100-17N
U6: 24LC16T-I/OT; SOT95P290X145-5N
U7: MCP4822-E/SN; SOIC8-N_MC
U$1: SWITCH_W_LED_PB6149L-X-102YELLOW; PB6149L

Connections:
3.3V: C4.2, C7.2, C8.2, C10.2, C12.+, C14.2, C17.1, C20.2, C21.2, D3.+, D40.+, IC1.2, IC1.4, IC4.4, R17.P$3, R20.2, R29.1, R42.P$3, R44.P$3, R45.P$3, R50.1, R51.1, R68.P$3, R69.P$3, R73.2, SWD1.1, U1.3, U3.10, U3.16, U4.10, U4.16, U5.10, U5.16, U6.4, U7.1
12V: C11.2, C13.+, C18.2, D1.2, IC1.3, IC3.4, R19.2, R39.2
-12V: C5.-, C19.2, D2.1, IC3.11, R26.1
ADC_FREQ: C16.2, IC4.14, R22.1, U1.16
ADC_MOD: C1.2, IC4.1, R2.1, U1.21
ADC_NORMAL: R44.P$2, U1.9
ADC_PHASE: C9.2, IC4.7, R13.1, U1.10
ADC_PHASED: R45.P$2, U1.14
ADC_SHAPE: C15.2, IC4.8, R12.1, U1.15
CLOCK: U1.1, U3.11, U4.11, U5.11
CPU_RESET: R29.2, SWD1.10, U1.23
DACCS: U1.7, U7.2
DACSCK: U1.12, U7.3
DACSDI: U1.11, U7.4
GND: C4.1, C5.+, C6.1, C7.1, C8.1, C10.1, C11.1, C12.-, C13.-, C14.1, C17.2, C18.1, C19.1, C20.1, C21.1, D4.-, D5.-, D6.-, D7.-, D8.-, D9.-, D10.-, D11.-, D12.-, D24.-, D25.-, D26.-, D27.-, D28.-, D29.-, D30.-, D31.-, D32.-, D33.-, D34.-, D35.-, IC1.1, IC3.3, IC3.5, IC3.10, IC3.12, IC4.3, IC4.5, IC4.10, IC4.11, IC4.12, J1.RING@3, J1.SWITCH@3, J2.RING@3, J2.SWITCH@3, J3.RING@3, J3.SWITCH@3, J4.RING@3, J4.SWITCH@3, J5.RING@3, J5.SWITCH@3, J6.RING@3, J7.RING@3, J8.RING@3, J8.SWITCH@3, J12.RING@3, J13.RING@3, J14.3, J14.4, J14.5, J14.6, J14.7, J14.8, Q1.E, Q2.E, Q3.E, Q5.E, R17.P$1, R42.P$1, R44.P$1, R45.P$1, R68.P$1, R69.P$1, SWD1.3, SWD1.5, U1.4, U1.25, U2.1, U3.8, U3.13, U3.17, U4.8, U4.13, U4.17, U5.8, U5.13, U5.17, U6.2, U6.5, U7.5, U7.7, U$1.3, U$1.4, U$1.LEDNEG
KNOB_FREQ: R17.P$2, R30.2
KNOB_MOD: R27.2, R69.P$2
KNOB_PHASE: R42.P$2, R43.2
KNOB_SHAPE: R23.2, R68.P$2
LATCH: U1.19, U3.12, U4.12, U5.12
unnamed: R33.2, U5.15
unnamed: IC3.6, R4.2, R6.1
unnamed: J2.TIP@3, R16.2
unnamed: C15.1, IC4.9, R12.2, R15.1, R16.1, R23.1
unnamed: R9.2, U7.8
unnamed: J3.TIP@3, R1.2
unnamed: R7.2, U7.6
unnamed: C1.1, IC4.2, R1.1, R2.2, R3.1, R27.1
unnamed: C2.1, IC3.13, R5.2, R9.1, R37.1
unnamed: C3.1, IC3.2, R7.1, R8.2, R36.1
unnamed: J4.TIP@3, R11.2
unnamed: C9.1, IC4.6, R11.1, R13.2, R41.1, R43.1
unnamed: D1.1, J14.9, J14.10
unnamed: D7.+, R47.1
unnamed: Q1.B, R18.2
unnamed: J5.TIP@3, R18.1
unnamed: IC3.9, R52.1, R53.2
unnamed: C3.2, IC3.1, R4.1, R8.1
unnamed: R64.2, U5.1
unnamed: J13.TIP@3, R25.1
unnamed: J12.TIP@3, R24.1
unnamed: R63.2, U5.2
unnamed: D40.-, R10.1
unnamed: C2.2, IC3.14, R5.1, R53.1
unnamed: Q3.B, R21.2
unnamed: R61.2, U5.3
unnamed: D3.-, R35.1
unnamed: D28.+, R62.1
unnamed: J7.TIP@3, Q3.C, R19.1
unnamed: R62.2, U5.4
unnamed: R57.2, U5.5
unnamed: D29.+, R61.1
unnamed: J1.TIP@3, R14.2
unnamed: C16.1, IC4.13, R14.1, R22.2, R28.1, R30.1
unnamed: R56.2, U5.6
unnamed: R58.2, U5.7
unnamed: R59.2, U4.3
unnamed: R54.2, U3.7
unnamed: R55.2, U3.6
unnamed: R47.2, U3.5
unnamed: R38.1, U$1.LEDPOS
unnamed: RX.TP, U1.13
unnamed: R46.2, U3.4
unnamed: Q2.B, R72.2
unnamed: J8.TIP@3, R72.1
unnamed: D6.+, R46.1
unnamed: D5.+, R48.1
unnamed: D4.+, R49.1
unnamed: D8.+, R55.1
unnamed: D9.+, R54.1
unnamed: D10.+, R60.1
unnamed: D11.+, R65.1
unnamed: R48.2, U3.3
unnamed: R49.2, U3.2
unnamed: R32.2, U3.1
unnamed: R65.2, U3.15
unnamed: R60.2, U4.7
unnamed: R34.2, U4.1
unnamed: R31.2, U4.2
unnamed: Q5.B, R40.2
unnamed: J6.TIP@3, Q5.C, R39.1
unnamed: R66.2, U4.15
unnamed: D2.2, J14.1, J14.2
unnamed: D12.+, R66.1
unnamed: D27.+, R57.1
unnamed: D26.+, R56.1
unnamed: D25.+, R58.1
unnamed: D24.+, R59.1
unnamed: D30.+, R63.1
unnamed: D31.+, R64.1
unnamed: D32.+, R33.1
unnamed: D33.+, R32.1
unnamed: D34.+, R31.1
unnamed: D35.+, R34.1
NORMALOUT: IC3.7, R6.2, R24.2
OUT_LFOCYCLEMID: R10.2, R21.1, U4.5
OUT_LFOCYCLESTART: R35.2, R40.1, U4.4
PHASEDOUT: IC3.8, R25.2, R52.2
REF_-5V: C6.2, R3.2, R15.2, R26.2, R28.2, R36.2, R37.2, R41.2, U2.2
RESET_PATTERN: Q1.C, R20.1, U1.20, U$1.1, U$1.2
SCL: R50.2, U1.17, U6.1
SDA: R51.2, U1.18, U6.3
SHIFTER1TO2: U4.14, U5.9
SHIFTERS: U1.2, U5.14
SHIFTERS2TO3: U3.14, U4.9
SWD_CLK: SWD1.4, U1.22
SWD_DIO: SWD1.2, U1.24
SYNC_LFO: Q2.C, R73.1
TRIGGERBUTTONLED: R38.2, U4.6
